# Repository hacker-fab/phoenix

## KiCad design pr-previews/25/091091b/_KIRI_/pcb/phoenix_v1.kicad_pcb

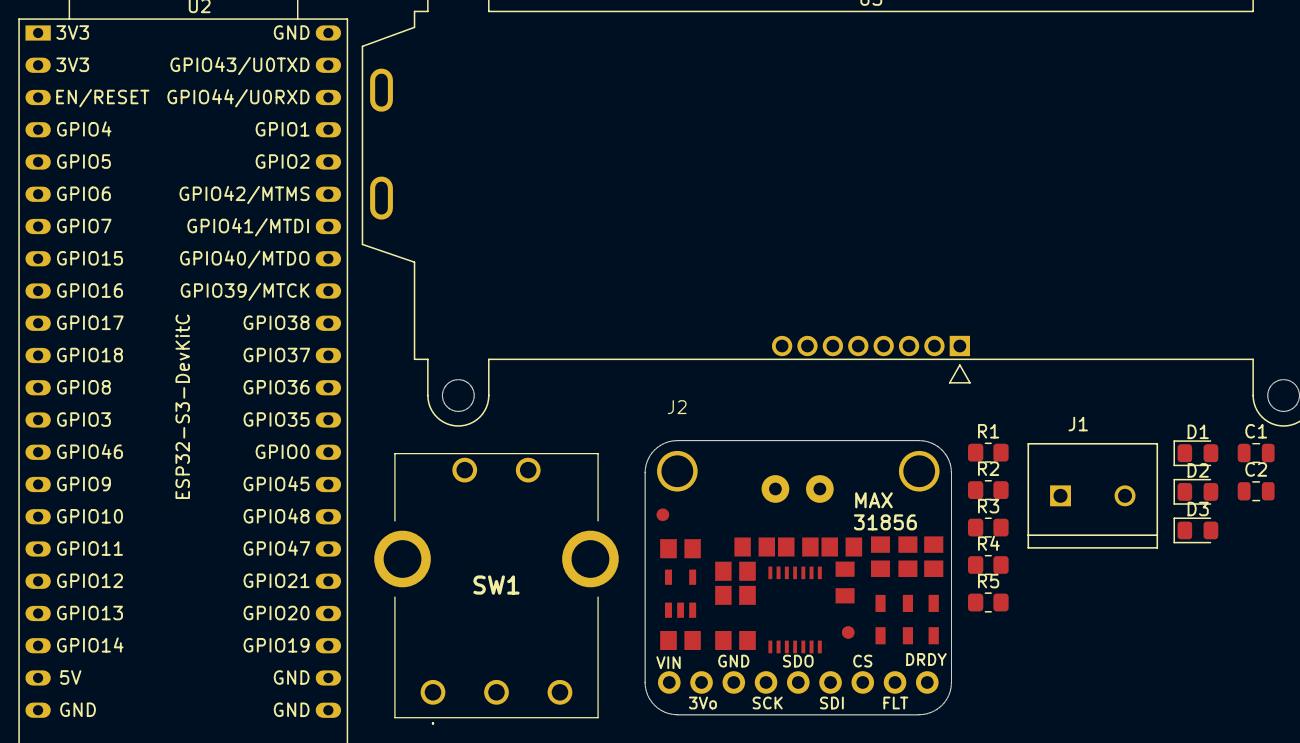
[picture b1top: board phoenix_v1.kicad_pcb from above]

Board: 2 copper layers, 15 parts (0 on the bottom side), 16 nets, no tracks yet.

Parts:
C1, C2: 1uF; C_0805_2012Metric
D1, D2, D3: LED; D_0805_2012Metric_Pad1.15x1.40mm_HandSolder
J1: Screw_Terminal_01x02; TE_282837-2
J2: Conn_01x09_Socket; MAX31856_HEADER
R1, R2, R3: 220; R_0805_2012Metric_Pad1.20x1.40mm_HandSolder
R4, R5: 4.7k; R_0805_2012Metric_Pad1.20x1.40mm_HandSolder
SW1: RotaryEncoder_Switch; PEC164120FS0012
U2: ESP32-S3-DevKitC
U3: NHD-C0220BIZ; NHD-C0220BiZ

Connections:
+3.3V: J2.8, R4.1, R5.1, U2.1 (3V3), U2.2 (3V3)
+5V: C1.1, U2.21 (5V), U3.5 (VDD)
/DISPLAY_~RST: U2.32 (GPIO35), U3.1 (~RST)
/SCL: R4.2, U2.5 (GPIO5/ADC1_CH4), U3.2 (SCL)
/SDA: R5.2, U2.4 (GPIO4/ADC1_CH3), U3.3 (SDA)
GND: D1.1 (K), D2.1 (K), D3.1 (K), J1.1, J2.7, U2.22 (GND), U2.23 (GND), U2.24 (GND), U2.44 (GND), U3.4 (VSS)
unnamed: D1.2 (A), R1.2
unnamed: D2.2 (A), R2.2
unnamed: D3.2 (A), R3.2
unnamed: R1.1, U2.14 (GPIO46)
unnamed: R2.1, U2.28 (GPIO47)
unnamed: R3.1, U2.29 (GPIO48)
unnamed: C2.1, U3.7 (C1+)
unnamed: C2.2, U3.8 (C1-)
unnamed: C1.2, U3.6 (VOUT)
SSR_PWM: J1.2, U2.27 (GPIO21)
